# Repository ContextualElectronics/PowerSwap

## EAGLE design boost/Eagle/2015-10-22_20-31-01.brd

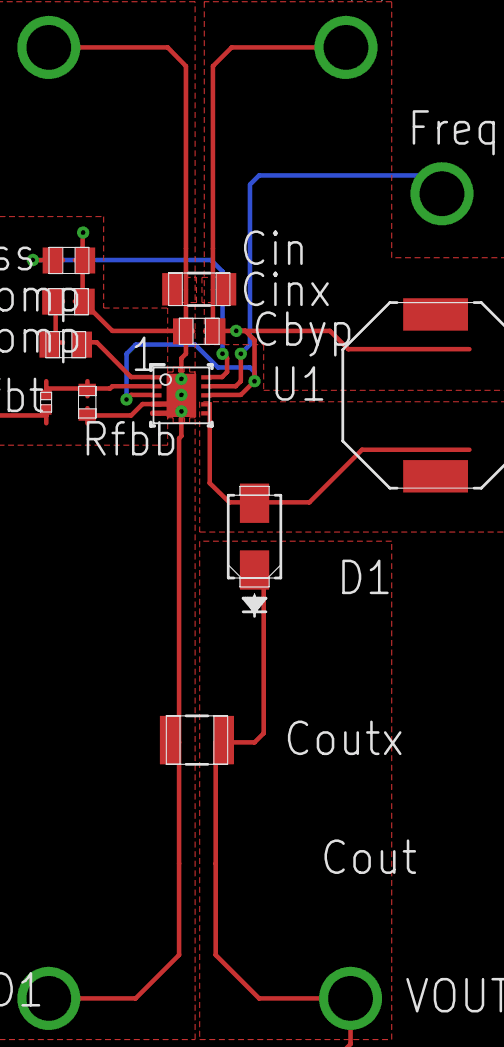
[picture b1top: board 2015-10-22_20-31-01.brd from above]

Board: 4 copper layers, 16 parts (0 on the bottom side), 9 nets.

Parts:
Cbyp: 0805
Ccomp: 0805
Cin: 1206
Cout: 1210
Css: 0805
D1: SMA
Freq: TP-1502
GND, GND1: TP-1502
L1: SRU1048
Rcomp: 0805
Rfbb: 0603
Rfbt: 0402
U1: DRC0010A
VIN: TP-1502
VOUT: TP-1502

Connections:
0: Cbyp.2, Ccomp.2, Cin.2, Cout.2, Css.2, GND.1, GND1.1, Rfbb.2, U1.4, U1.5, U1.11
1: Cbyp.1, Cin.1, L1.1, U1.3, U1.8, VIN.1
2: Cout.1, D1.1, Rfbt.1, VOUT.1
4: D1.2, L1.2, U1.6, U1.7
5: Rcomp.1, U1.1
6: Rfbb.1, Rfbt.2, U1.2
7: Ccomp.1, Rcomp.2
13: Freq.1, U1.9
14: Css.1, U1.10

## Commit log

2015-08-01 Added TPS63030 component plus passives
2015-08-09 Added values to schematic and added inductor footprint
2015-08-09 Added TPS63030 Footprint
2015-08-09 Imported footprints
2015-08-10 Finished Power Swap Layout
2015-08-13 Added via stitching and generated gerbers for fabrication
2015-10-23 Moved previous design to buck-boost folder, created boost folder
2015-10-23 Added BOM and EAGLE layout from web bench
2015-10-29 Added components as shown in example schematic on TPS61087 datasheet
2015-11-02 Added footprints to layout
2015-11-04 Updated component values
2015-11-04 Added EAGLE files from WebBench output
2015-11-04 Initial Layout
2015-11-05 Finished layout
2015-11-08 Added indicator LED, mounting holes and a logo.
2015-11-08 Gerber generation for Rev 1 proto
